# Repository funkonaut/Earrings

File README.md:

# Earrings
Light up earring art.

[Check out the project website here](https://funkonaut.github.io/project_doc/)

# Design Files
.brd and .sch files availble for EAGLE CAD. 

For each design folder there is also:
- Images of the physical boards
- .step 3D models
- Rendered images of the top and bottom of the board
- A BOM (bill of materials) for the design

# Doc
You can find a prefab checklist and some notes on design rules/process in the .csv and .pdfs. 

There is also a project write up that goes into detail on the design, assembly, and marketing/sales processes that went into this project.

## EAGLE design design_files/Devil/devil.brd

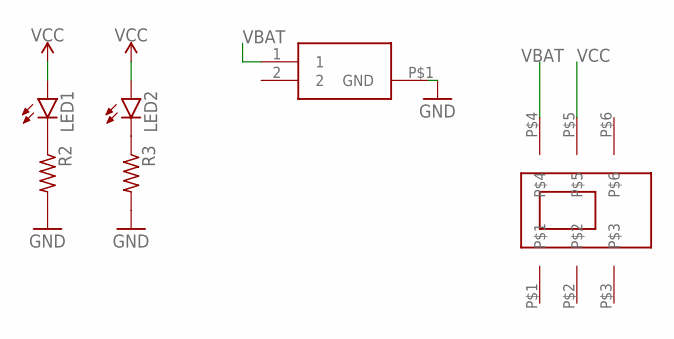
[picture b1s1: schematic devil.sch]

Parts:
LED1, LED2: LEDCHIP-LED0603; CHIP-LED0603
R2, R3: R-US_R0603; R0603
U$1: CL-SB-22A-02T-SLIDE-SWITCH-TUCKED-PADS; CL-SB-22A-02T-DPDT-COMPACT-SWITCH
VBAT: BAT-HLD-012-SMT; BATHLD012SMT

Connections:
GND: R2.2, R3.2, VBAT.P$1 (GND)
unnamed: LED1.C, R2.1
unnamed: LED2.C, R3.1
VBAT: U$1.P$4, VBAT.1
VCC: LED1.A, LED2.A, U$1.P$5

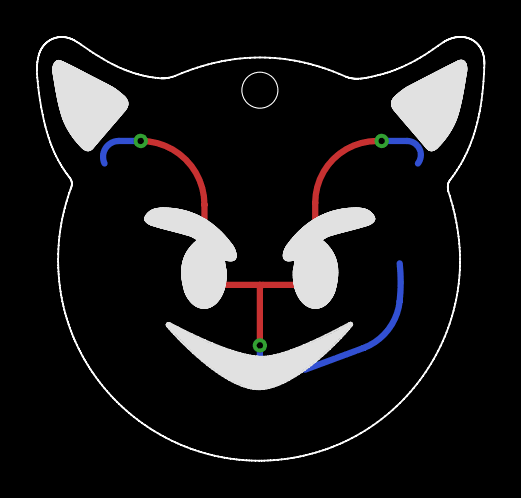
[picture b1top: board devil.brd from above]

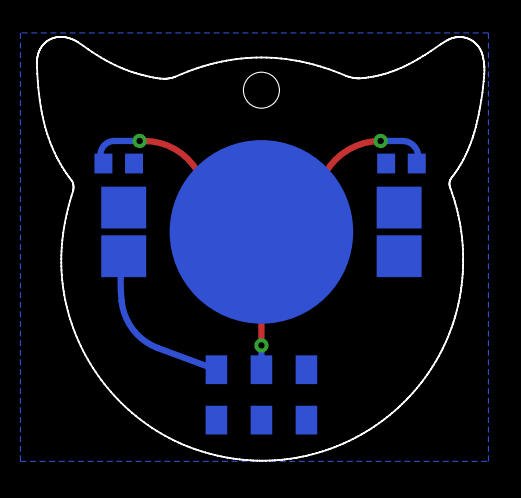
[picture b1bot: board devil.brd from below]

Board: 2 copper layers, 24.9 x 23.5 mm, 6 parts (4 on the bottom side), 5 nets.

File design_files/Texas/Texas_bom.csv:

Part,Value,Device,Package,Description,HEIGHT,MANUFACTURER_NAME,MANUFACTURER_PART_NUMBER,MOUSER_PART_NUMBER,MOUSER_PRICE-STOCK,POPULARITY,SPICEPREFIX,
LED1,,LEDCHIP-LED0805,CHIP-LED0805,LED,,,,,,68,,
R2,,R-US_R0603,R0603,"RESISTOR, American symbol",,,,,,77,R,
U$1,CL-SB-22A-02T-SLIDE-SWITCH-TUCKED-PADS,CL-SB-22A-02T-SLIDE-SWITCH-TUCKED-PADS,CL-SB-22A-11T side setting,(names in device are wrong),,,,,,,,
VBAT,BAT-HLD-012-SMT,BAT-HLD-012-SMT,BATHLD012SMT,Coin Cell Battery Holders Bat Hld CR1216/1225 Surface Mount,3mm,Linx Technologies,BAT-HLD-012-SMT,712-BAT-HLD-012-SMT,https://www.mouser.com/Search/Refine.aspx?Keyword=712-BAT-HL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,,,

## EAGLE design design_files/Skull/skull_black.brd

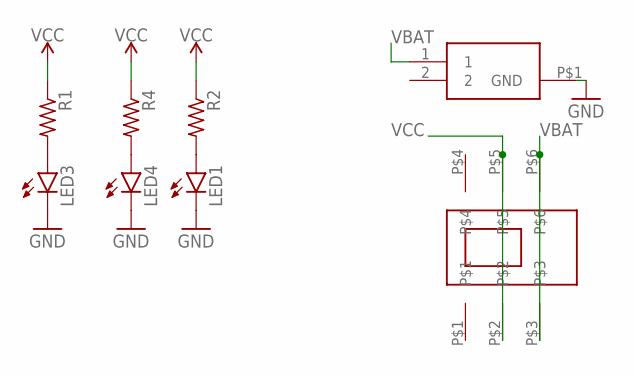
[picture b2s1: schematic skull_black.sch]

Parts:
LED1, LED3, LED4: LEDCHIP-LED0805; CHIP-LED0805
R1, R2, R4: R-US_R0603; R0603
U$1: CL-SB-22A-02T-SLIDE-SWITCH-TUCKED-PADS; CL-SB-22A-02T-DPDT-COMPACT-SWITCH
VBAT: BAT-HLD-012-SMT; BATHLD012SMT

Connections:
GND: LED1.C, LED3.C, LED4.C, VBAT.P$1 (GND)
unnamed: LED1.A, R2.2
unnamed: LED3.A, R1.2
unnamed: LED4.A, R4.2
VBAT: U$1.P$3, U$1.P$6, VBAT.1
VCC: R1.1, R2.1, R4.1, U$1.P$2, U$1.P$5

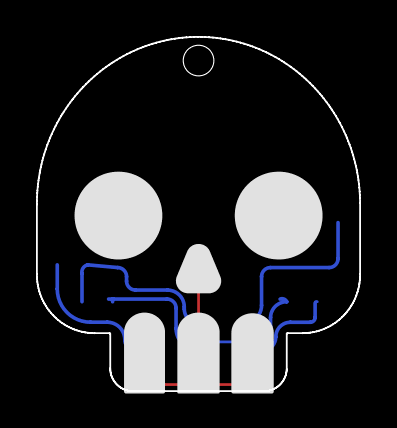
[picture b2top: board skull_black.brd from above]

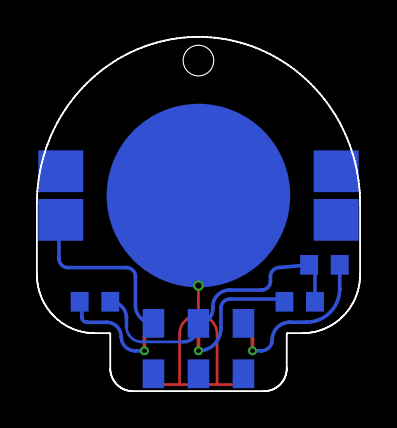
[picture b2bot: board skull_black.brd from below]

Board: 2 copper layers, 18.0 x 19.7 mm, 8 parts (5 on the bottom side), 6 nets.

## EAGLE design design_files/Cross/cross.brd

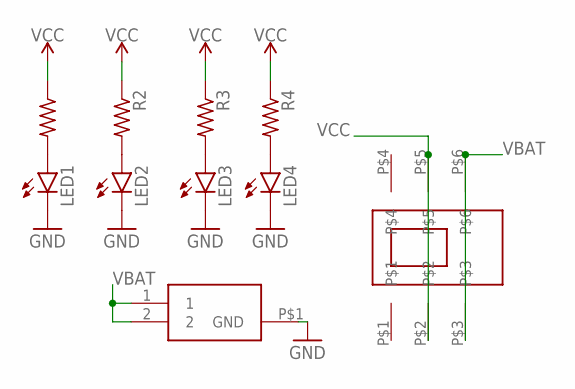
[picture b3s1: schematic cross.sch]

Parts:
LED1, LED2, LED3, LED4: LEDCHIP-LED0805; CHIP-LED0805
R1, R2, R3, R4: R-US_R0603; R0603
U$1: CL-SB-22A-02T-SLIDE-SWITCH-TUCKED-PADS; CL-SB-22A-02T-DPDT-COMPACT-SWITCH
VBAT: BAT-HLD-012-SMT; BATHLD012SMT

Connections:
GND: LED1.C, LED2.C, LED3.C, LED4.C, VBAT.P$1 (GND)
unnamed: LED1.A, R1.2
unnamed: LED2.A, R2.2
unnamed: LED3.A, R3.2
unnamed: LED4.A, R4.2
VBAT: U$1.P$3, U$1.P$6, VBAT.1, VBAT.2
VCC: R1.1, R2.1, R3.1, R4.1, U$1.P$2, U$1.P$5

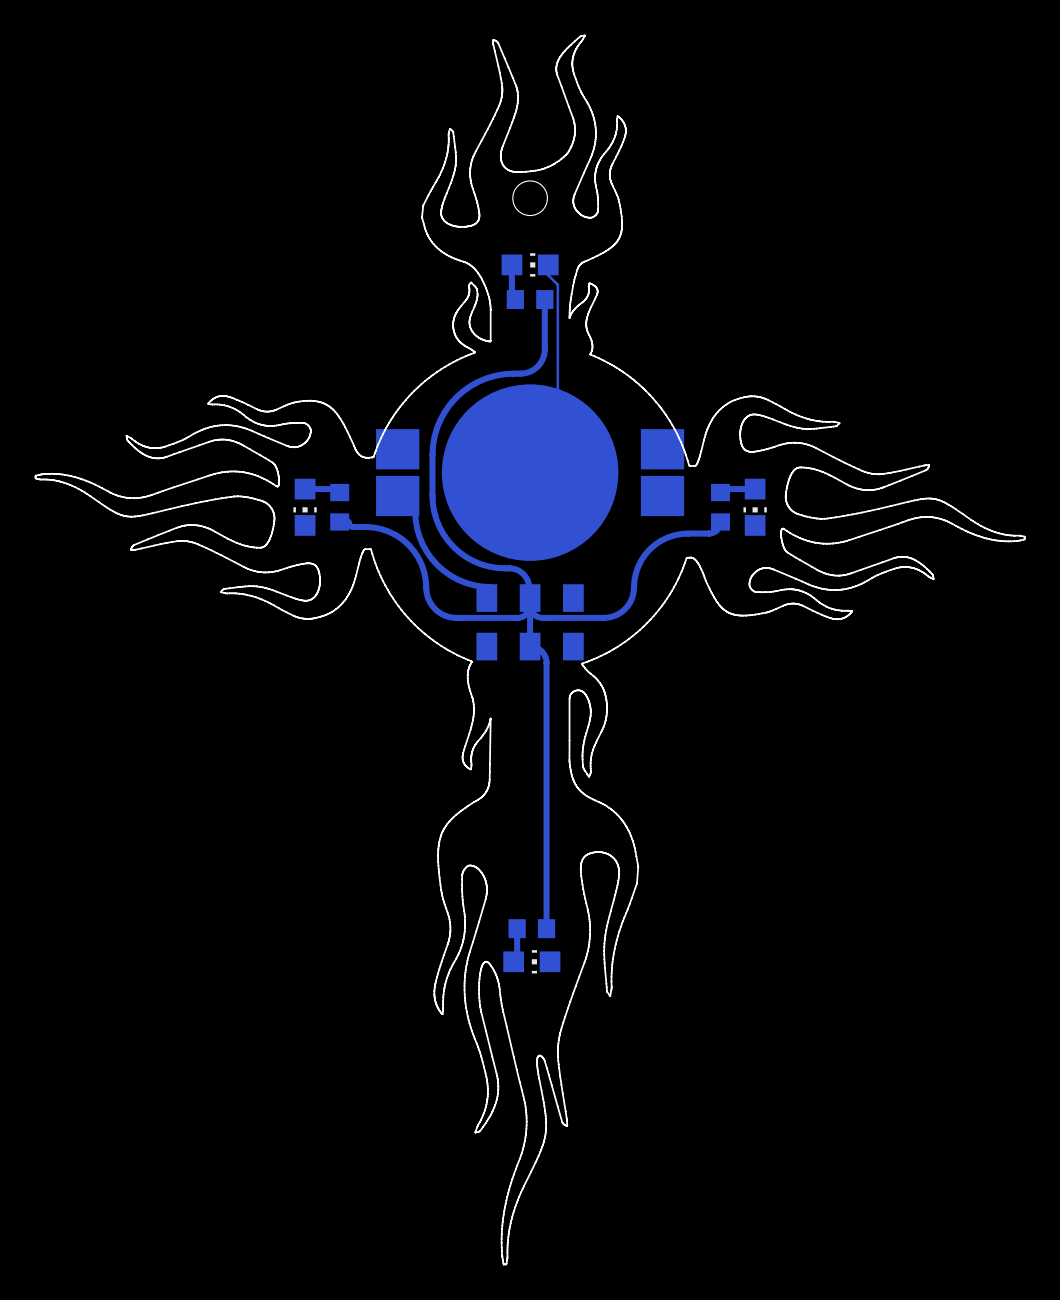
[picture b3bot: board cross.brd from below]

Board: 2 copper layers, 57.1 x 71.0 mm, 10 parts (10 on the bottom side), 7 nets.

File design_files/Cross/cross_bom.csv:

Part,Value,Device,Package,Description,HEIGHT,MANUFACTURER_NAME,MANUFACTURER_PART_NUMBER,MOUSER_PART_NUMBER,MOUSER_PRICE-STOCK,POPULARITY,SPICEPREFIX,
LED1,,LEDCHIP-LED0805,CHIP-LED0805,LED,,,,,,68,,
LED2,,LEDCHIP-LED0805,CHIP-LED0805,LED,,,,,,68,,
LED3,,LEDCHIP-LED0805,CHIP-LED0805,LED,,,,,,68,,
LED4,,LEDCHIP-LED0805,CHIP-LED0805,LED,,,,,,68,,
R1,,R-US_R0603,R0603,"RESISTOR, American symbol",,,,,,77,R,
R2,,R-US_R0603,R0603,"RESISTOR, American symbol",,,,,,77,R,
R3,,R-US_R0603,R0603,"RESISTOR, American symbol",,,,,,77,R,
R4,,R-US_R0603,R0603,"RESISTOR, American symbol",,,,,,77,R,
U$1,CL-SB-22A-02T-SLIDE-SWITCH-TUCKED-PADS,CL-SB-22A-02T-SLIDE-SWITCH-TUCKED-PADS,CL-SB-22A-11T side setting,(names in device are wrong),,,,,,,,
VBAT,BAT-HLD-012-SMT,BAT-HLD-012-SMT,BATHLD012SMT,Coin Cell Battery Holders Bat Hld CR1216/1225 Surface Mount,3mm,Linx Technologies,BAT-HLD-012-SMT,712-BAT-HLD-012-SMT,https://www.mouser.com/Search/Refine.aspx?Keyword=712-BAT-HL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,,,

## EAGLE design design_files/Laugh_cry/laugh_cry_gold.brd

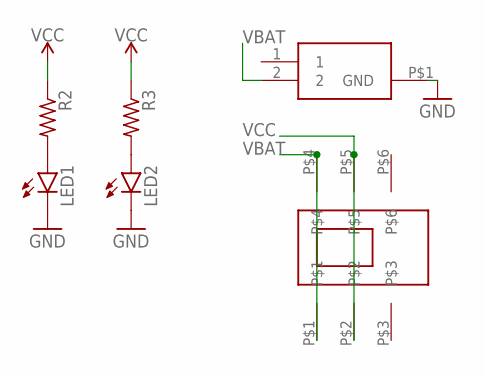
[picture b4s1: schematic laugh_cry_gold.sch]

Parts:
LED1, LED2: LEDCHIP-LED0805; CHIP-LED0805
R2, R3: R-US_R0603; R0603
U$1: CL-SB-22A-02T-SLIDE-SWITCH-TUCKED-PADS; CL-SB-22A-02T-DPDT-COMPACT-SWITCH
VBAT: BAT-HLD-012-SMT; BATHLD012SMT

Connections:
GND: LED1.C, LED2.C, VBAT.P$1 (GND)
unnamed: LED1.A, R2.2
unnamed: LED2.A, R3.2
VBAT: U$1.P$1, U$1.P$4, VBAT.2
VCC: R2.1, R3.1, U$1.P$2, U$1.P$5

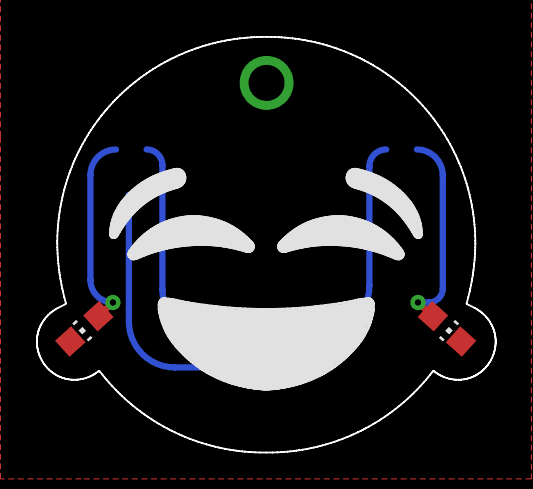
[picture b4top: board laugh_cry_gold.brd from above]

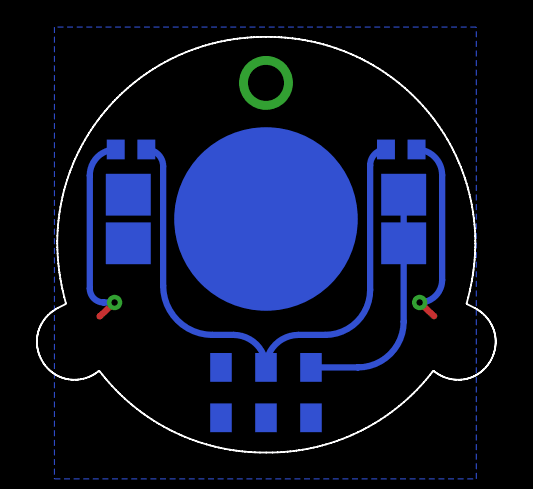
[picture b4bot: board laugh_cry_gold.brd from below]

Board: 2 copper layers, 25.5 x 23.1 mm, 6 parts (4 on the bottom side), 5 nets.

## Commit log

2021-01-02 Design Files
2021-01-02 README
2021-11-27 adds alien devil pictures
2021-12-10 adds updates and pics
2021-12-10 adds website doc
2021-12-10 adds write up
2021-12-10 fix readme url to webpage
2022-01-10 Create LICENSE
2022-01-21 all hands design

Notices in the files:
parts and their libraries:
SparkFun-PowerSymbols: Licensing: Creative Commons ShareAlike 4.0 International - https://creativecommons.org/licenses/by-sa/4.0
